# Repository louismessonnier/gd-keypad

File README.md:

# gd-keypad

A custom analog macropad for **Geometry Dash**, built around magnetic Hall-effect switches for continuous key-travel sensing — the same technology used in Wooting and SayoDevice keyboards.

<!-- TODO: hero image of the assembled board or a KiCad 3D render -->
<!--  -->

---

## Overview

<!-- TODO: 2–3 sentences. What it is, why you built it, what makes it interesting.
Suggested points to cover:
- Hall-effect switches measure how far a key has travelled, not just pressed/not-pressed
- This enables rapid trigger and adjustable actuation, which matter in a timing-based game
- Compact macropad form factor: 3 analog jump keys + 6 mechanical keys + rotary encoder -->

## Features

<!-- TODO: trim/expand as needed -->
- **3 analog Hall-effect keys** with per-key position sensing (rapid trigger, adjustable actuation point)
- **6 mechanical keys** in a diode matrix
- **Rotary encoder** for per-application volume control in Geometry Dash
- **8 kHz USB polling** via the AT32F405's high-speed USB
- USB-C connector, DFU flashing (no external programmer required)
- Configurable through the [hmkconf](https://hmkconf.com/) web tool

## Hardware

<!-- TODO: confirm/adjust each line against your final BOM -->
- **MCU:** Artery AT32F405RCT7 (Cortex-M4F, LQFP-64)
- **Analog switches:** <!-- final switch choice --> with <!-- final sensor, e.g. SS39ET --> linear Hall sensors
- **Mechanical switches:** <!-- hotswap socket type + switch --> 
- **Rotary encoder:** <!-- final encoder part number -->
- **PCB:** 2-layer, 1.2 mm, designed in KiCad, manufactured by JLCPCB

<!-- Optional: a few design highlights that show depth. Examples:
- Separate low-noise LDO for the analog supply to keep the ADC reference clean
- Dedicated 12 MHz crystal required by the high-speed USB PHY
- Solid ground plane opposite the MCU for tight decoupling return paths -->

## Firmware

This board runs [libhmk](https://github.com/peppapighs/libhmk), an open-source Hall-effect keyboard firmware. Analog behaviour (actuation points, rapid trigger, key mapping) is configured at runtime through [hmkconf](https://hmkconf.com/).

On top of the base firmware, this project adds:
- <!-- TODO --> Mechanical matrix scanning
- <!-- TODO --> Rotary encoder handling (volume via F13/F14)
- <!-- TODO --> A companion PC script (AutoHotkey + SoundVolumeView) for per-application Geometry Dash volume control

<!-- TODO: note what is implemented vs planned -->

## Repository layout

<!-- TODO: adjust descriptions to match what actually ends up in each folder -->
```
cad/        Case and knob models
docs/       Design notes and documentation
images/     Renders and photos
kicad/      KiCad project (schematic + PCB)
libraries/  KiCad symbol/footprint libraries used by the project
```

## Build / usage

<!-- TODO: fill in once the board is assembled and firmware is written.
Suggested sections:
- Ordering the PCB (JLCPCB, board settings, BOM/CPL)
- Bill of materials
- Assembly notes (which parts are hand-soldered)
- Flashing the firmware (DFU: hold BOOT0, plug in USB, flash with STM32CubeProgrammer / WebUSB DFU)
- Configuring with hmkconf
- Setting up the volume-control script -->

## Design notes

<!-- Optional but strong for a portfolio. A few bullets on decisions and what you learned.
Examples from this build:
- Why an analog/Hall-effect board over a standard mechanical one
- The two-LDO split for analog supply isolation
- Why the crystal must be 12 MHz (fixed input to the USB high-speed PLL)
- Building on an existing open-source design (HE60) vs designing from scratch -->

## Acknowledgements

This project builds on the work of others in the open-source Hall-effect keyboard community:

- **[libhmk](https://github.com/peppapighs/libhmk)** and **[HE60](https://github.com/peppapighs/HE60)** by [peppapighs](https://github.com/peppapighs) — firmware and reference hardware design that this board is based on
- **[marbastlib](https://github.com/ebastler/marbastlib)** by [ebastler](https://github.com/ebastler) — KiCad footprint library for the Hall-effect and mechanical switches

## License

<!-- TODO: choose a license. MIT is a common, permissive choice for hardware/firmware portfolio projects.
Note: if you reuse or adapt files from libhmk / HE60 / marbastlib, check and respect their licenses. -->

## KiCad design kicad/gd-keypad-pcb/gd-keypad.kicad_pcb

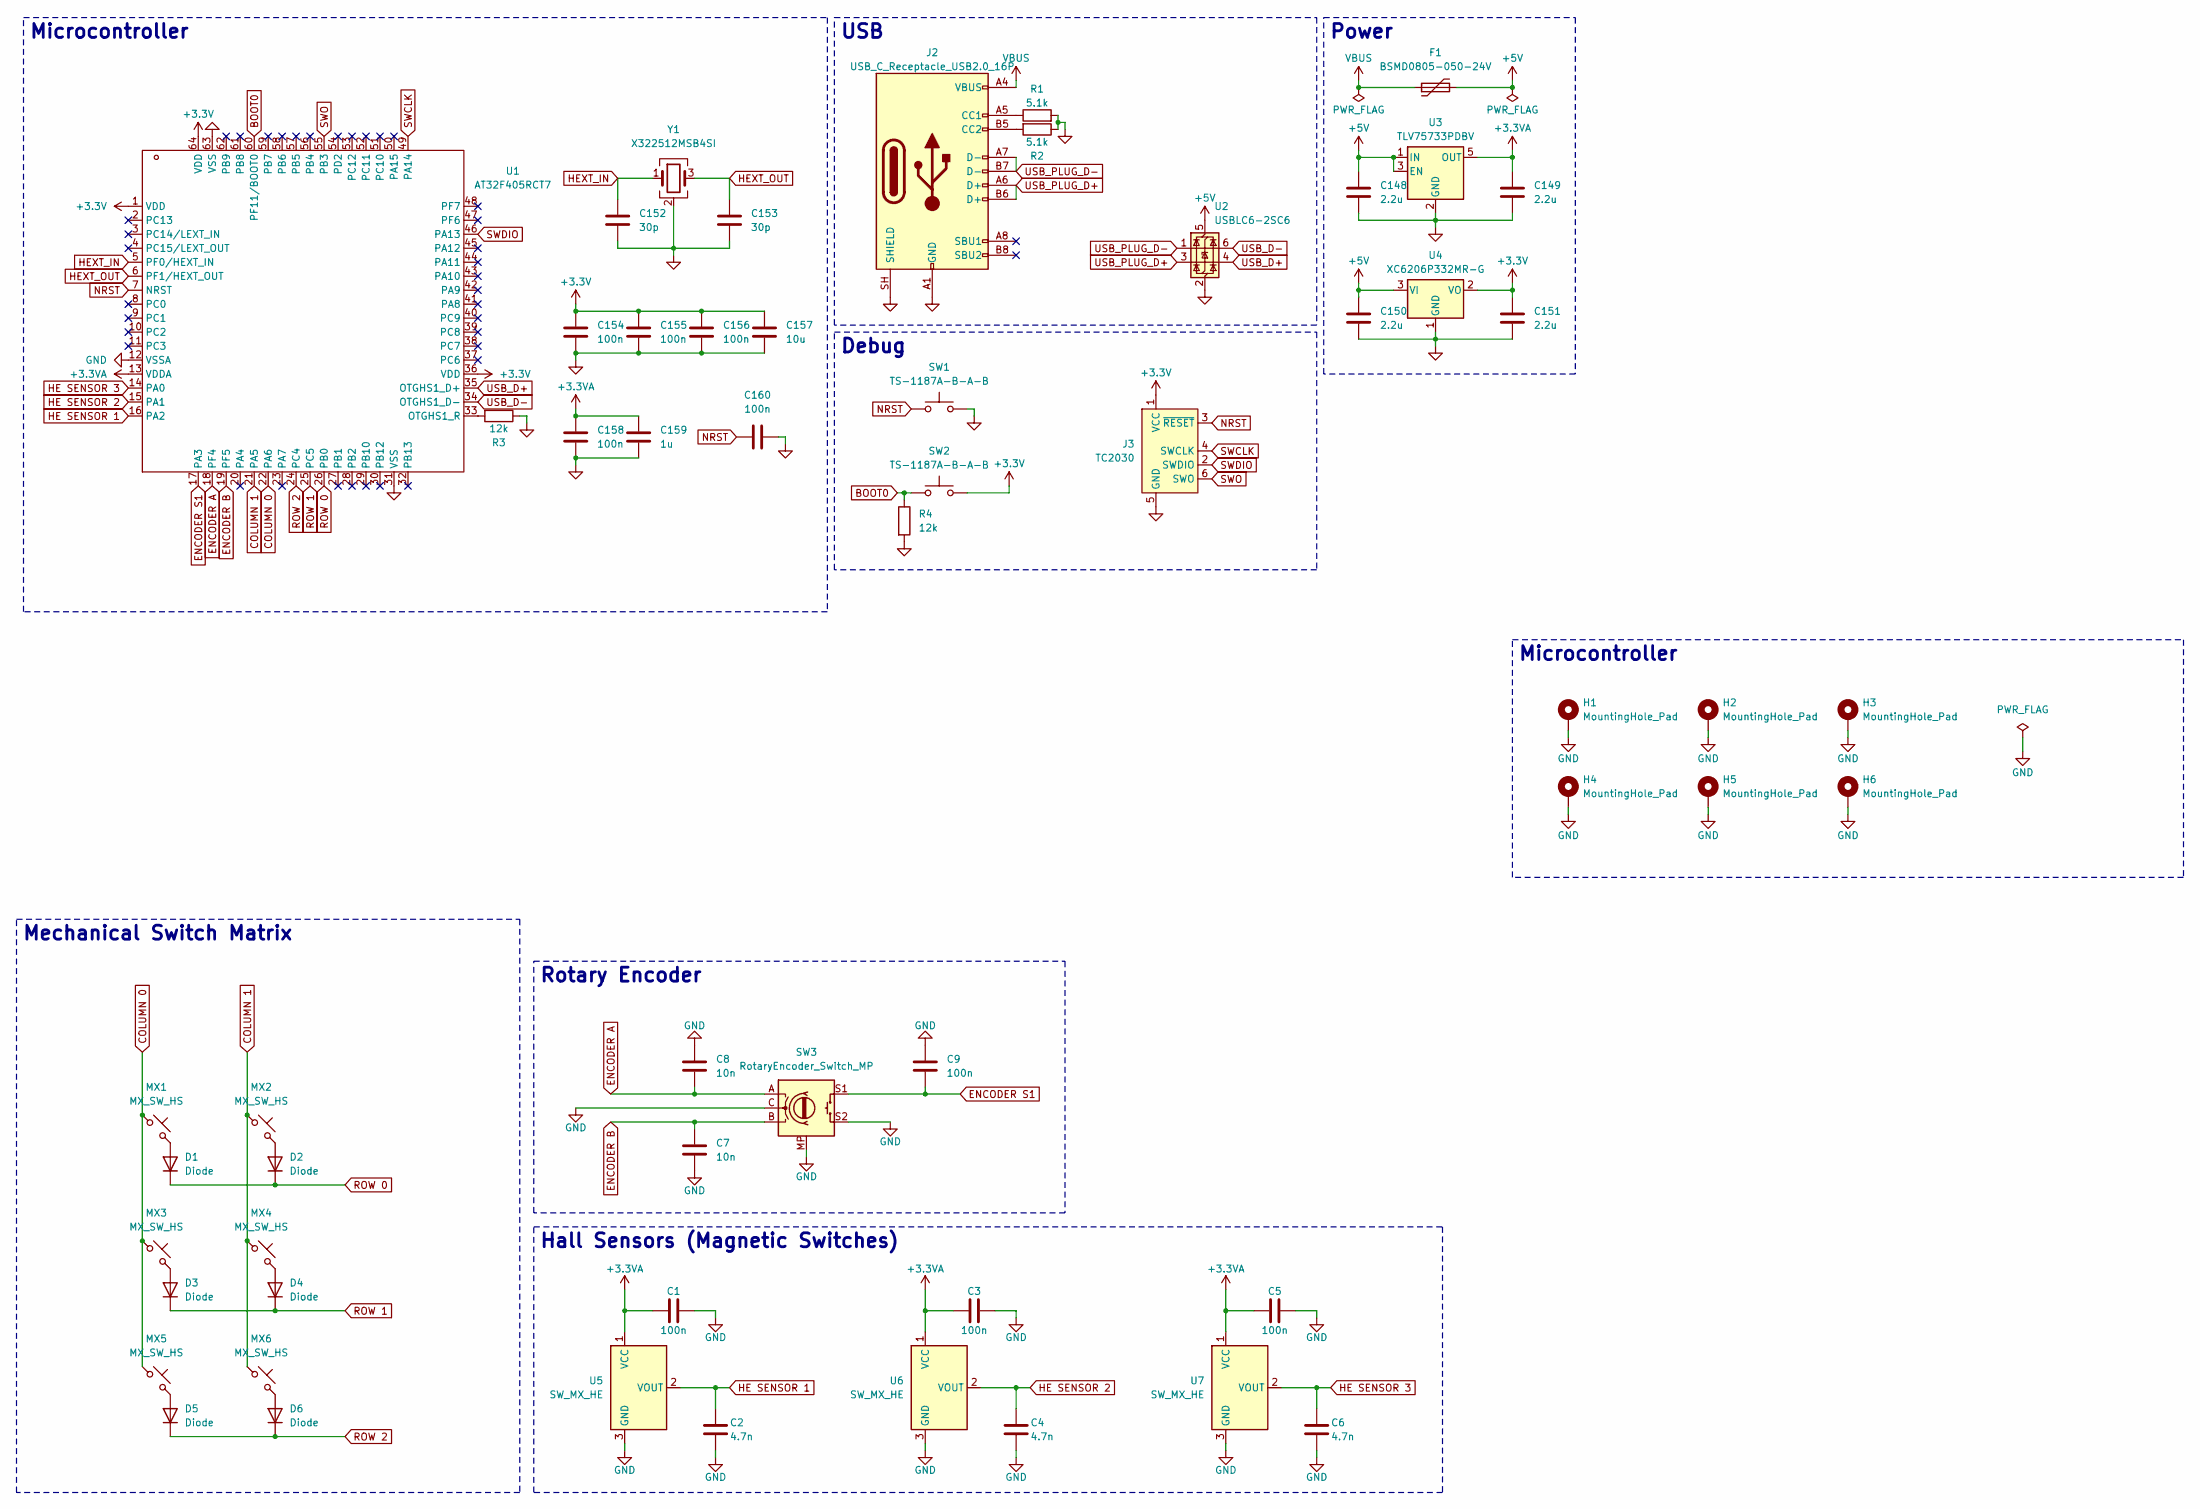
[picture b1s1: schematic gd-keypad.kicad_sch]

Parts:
C1, C3, C5, C9, C154, C155, C156, C158, C160: 100n; C_0402_1005Metric
C2, C4, C6: 4.7n; C_0402_1005Metric
C7, C8: 10n; C_0402_1005Metric
C148, C149, C150, C151: 2.2u; C_0603_1608Metric
C152, C153: 30p; C_0603_1608Metric
C157: 10u; C_0603_1608Metric
C159: 1u; C_0603_1608Metric
D1, D2, D3, D4, D5, D6: Diode; D_SOD-123
F1: BSMD0805-050-24V; Fuse_0805_2012Metric
H1, H2, H3, H4, H5, H6: MountingHole_Pad; MountingHole_2.7mm_M2.5_DIN965_Pad
J2: USB_C_Receptacle_USB2.0_16P; USB_C_Receptacle_HRO_TYPE-C-31-M-12
J3: TC2030; Tag-Connect_TC2030-IDC-FP_2x03_P1.27mm_Vertical
MX1, MX2, MX3, MX4, MX5, MX6: MX_SW_HS; SW_MX_HS_KS-2P02B01-01_1u
R1, R2: 5.1k; R_0402_1005Metric
R3, R4: 12k; R_0402_1005Metric
SW1, SW2: TS-1187A-B-A-B; SW_Push_1P1T_XKB_TS-1187A
SW3: RotaryEncoder_Switch_MP; ROT_Alps_EC11E-Switch
U1: AT32F405RCT7; LQFP-64_10x10mm_P0.5mm
U2: USBLC6-2SC6; SOT-23-6
U3: TLV75733PDBV; SOT-23-5
U4: XC6206P332MR-G; SOT-23-3
U5, U6, U7: SW_MX_HE; SW_MX_HE_0deg_1u
Y1: X322512MSB4SI; Crystal_SMD_3225-4Pin_3.2x2.5mm

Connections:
+3.3V: C151.1, C154.1, C155.1, C156.1, C157.1, J3.1 (VCC), SW2.2, U1.1 (VDD), U1.36 (VDD), U1.64 (VDD), U4.2 (VO)
+3.3VA: C1.1, C3.1, C5.1, C149.1, C158.1, C159.1, U1.13 (VDDA), U3.5 (OUT), U5.1 (VCC), U6.1 (VCC), U7.1 (VCC)
+5V: C148.1, C150.1, F1.2, U2.5 (VBUS), U3.1 (IN), U3.3 (EN), U4.3 (VI)
BOOT0: R4.1, SW2.1, U1.60 (PF11/BOOT0)
COLUMN 0: MX1.1, MX3.1, MX5.1, U1.22 (PA6)
COLUMN 1: MX2.1, MX4.1, MX6.1, U1.21 (PA5)
ENCODER A: C8.2, SW3.A, U1.18 (PF4)
ENCODER B: C7.1, SW3.B, U1.19 (PF5)
ENCODER S1: C9.1, SW3.S1, U1.17 (PA3)
GND: C1.2, C2.1, C3.2, C4.1, C5.2, C6.1, C7.2, C8.1, C9.2, C148.2, C149.2, C150.2, C151.2, C152.2, C153.2, C154.2, C155.2, C156.2, C157.2, C158.2, C159.2, C160.2, H1.1 (1_1), H2.1 (1_1), H3.1 (1_1), H4.1 (1_1), H5.1 (1_1), H6.1 (1_1), J2.A1 (GND), J2.A12 (GND), J2.B1 (GND), J2.B12 (GND), J2.SH (SHIELD), J3.5 (GND), R1.2, R2.1, R3.1, R4.2, SW1.2, SW3.C, SW3.MP, SW3.S2, U1.12 (VSSA), U1.31 (VSS), U1.63 (VSS), U2.2 (GND), U3.2 (GND), U4.1 (GND), U5.3 (GND), U6.3 (GND), U7.3 (GND), Y1.2 (G), Y1.4 (G)
HE SENSOR 1: C2.2, U1.16 (PA2), U5.2 (VOUT)
HE SENSOR 2: C4.2, U1.15 (PA1), U6.2 (VOUT)
HE SENSOR 3: C6.2, U1.14 (PA0), U7.2 (VOUT)
HEXT_IN: C152.1, U1.5 (PF0/HEXT_IN), Y1.1
HEXT_OUT: C153.1, U1.6 (PF1/HEXT_OUT), Y1.3
NRST: C160.1, J3.3 (~RESET), SW1.1, U1.7 (NRST)
unnamed: D1.2 (A), MX1.2
unnamed: D2.2 (A), MX2.2
unnamed: D3.2 (A), MX3.2
unnamed: D4.2 (A), MX4.2
unnamed: D5.2 (A), MX5.2
unnamed: D6.2 (A), MX6.2
unnamed: J2.A5 (CC1), R1.1
unnamed: J2.B5 (CC2), R2.2
unnamed: R3.2, U1.33 (OTGHS1_R)
ROW 0: D1.1 (K), D2.1 (K), U1.26 (PB0)
ROW 1: D3.1 (K), D4.1 (K), U1.25 (PC5)
ROW 2: D5.1 (K), D6.1 (K), U1.24 (PC4)
SWCLK: J3.4 (SWCLK), U1.49 (PA14)
SWDIO: J3.2 (SWDIO), U1.46 (PA13)
SWO: J3.6 (SWO), U1.55 (PB3)
USB_D+: U1.35 (OTGHS1_D+), U2.4 (I/O2)
USB_D-: U1.34 (OTGHS1_D-), U2.6 (I/O1)
USB_PLUG_D+: J2.A6 (D+), J2.B6 (D+), U2.3 (I/O2)
USB_PLUG_D-: J2.A7 (D-), J2.B7 (D-), U2.1 (I/O1)
VBUS: F1.1, J2.A4 (VBUS), J2.A9 (VBUS), J2.B4 (VBUS), J2.B9 (VBUS)

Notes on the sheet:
Debug
Power
USB
Rotary Encoder
Microcontroller
Mechanical Switch Matrix
Hall Sensors (Magnetic Switches)

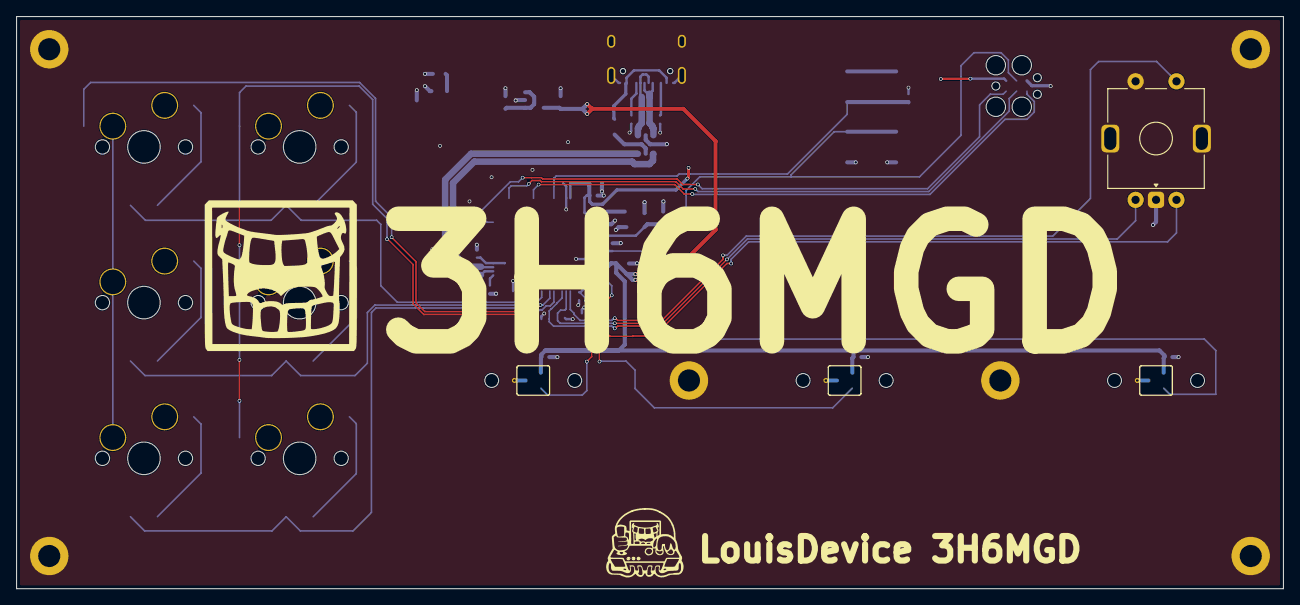
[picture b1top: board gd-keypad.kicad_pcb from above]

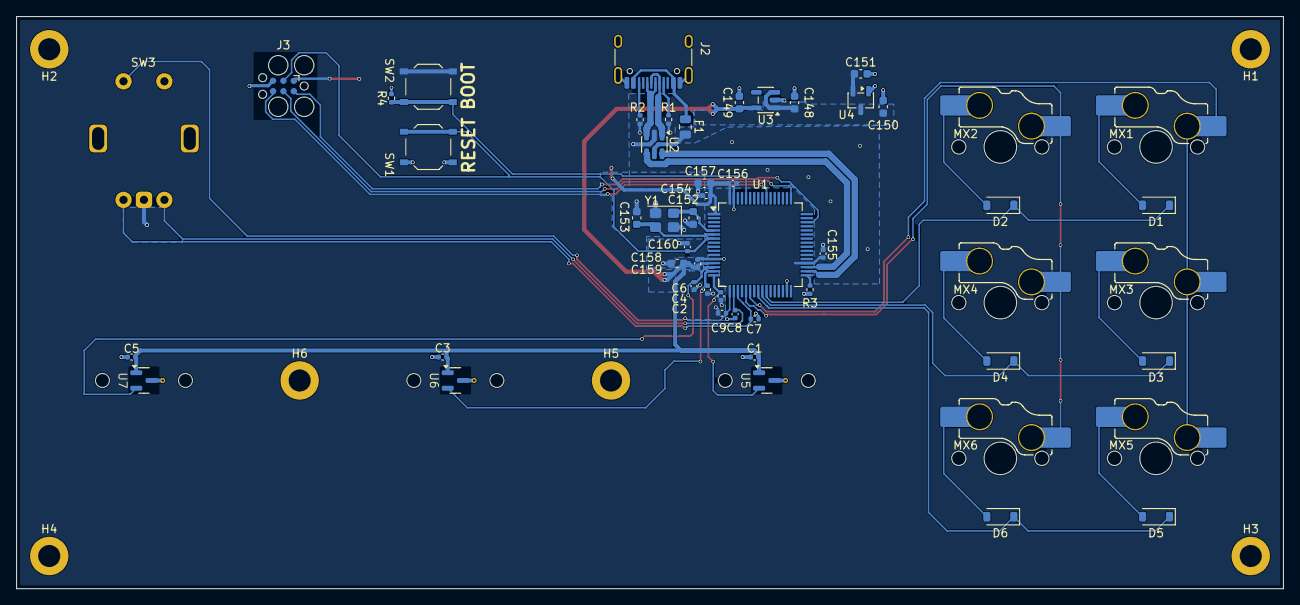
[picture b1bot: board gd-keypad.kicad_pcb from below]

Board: 2 copper layers, 155.0 x 70.0 mm, 58 parts (51 on the bottom side), 36 nets.

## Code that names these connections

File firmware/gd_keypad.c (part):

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#define GD_NUM_COLS 2
#define GD_NUM_MECH (GD_NUM_ROWS * GD_NUM_COLS)

// ROW 0 = PB0, ROW 1 = PC5, ROW 2 = PC4
static gpio_type *const row_ports[GD_NUM_ROWS] = {GPIOB, GPIOC, GPIOC};
static const uint16_t row_pins[GD_NUM_ROWS] = {
    GPIO_PINS_0,
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    GPIO_PINS_4,
};

// COLUMN 0 = PA6, COLUMN 1 = PA5
static gpio_type *const col_ports[GD_NUM_COLS] = {GPIOA, GPIOA};
static const uint16_t col_pins[GD_NUM_COLS] = {
    GPIO_PINS_6,
    GPIO_PINS_5,
};

// ENCODER A = PF4, ENCODER B = PF5, ENCODER S1 = PA3
#define GD_ENC_A_PORT GPIOF
#define GD_ENC_A_PIN GPIO_PINS_4
#define GD_ENC_B_PORT GPIOF
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

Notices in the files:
firmware/gd_keypad.c:
This program is free software: you can redistribute it and/or modify it under
the terms of the GNU General Public License as published by the Free Software
